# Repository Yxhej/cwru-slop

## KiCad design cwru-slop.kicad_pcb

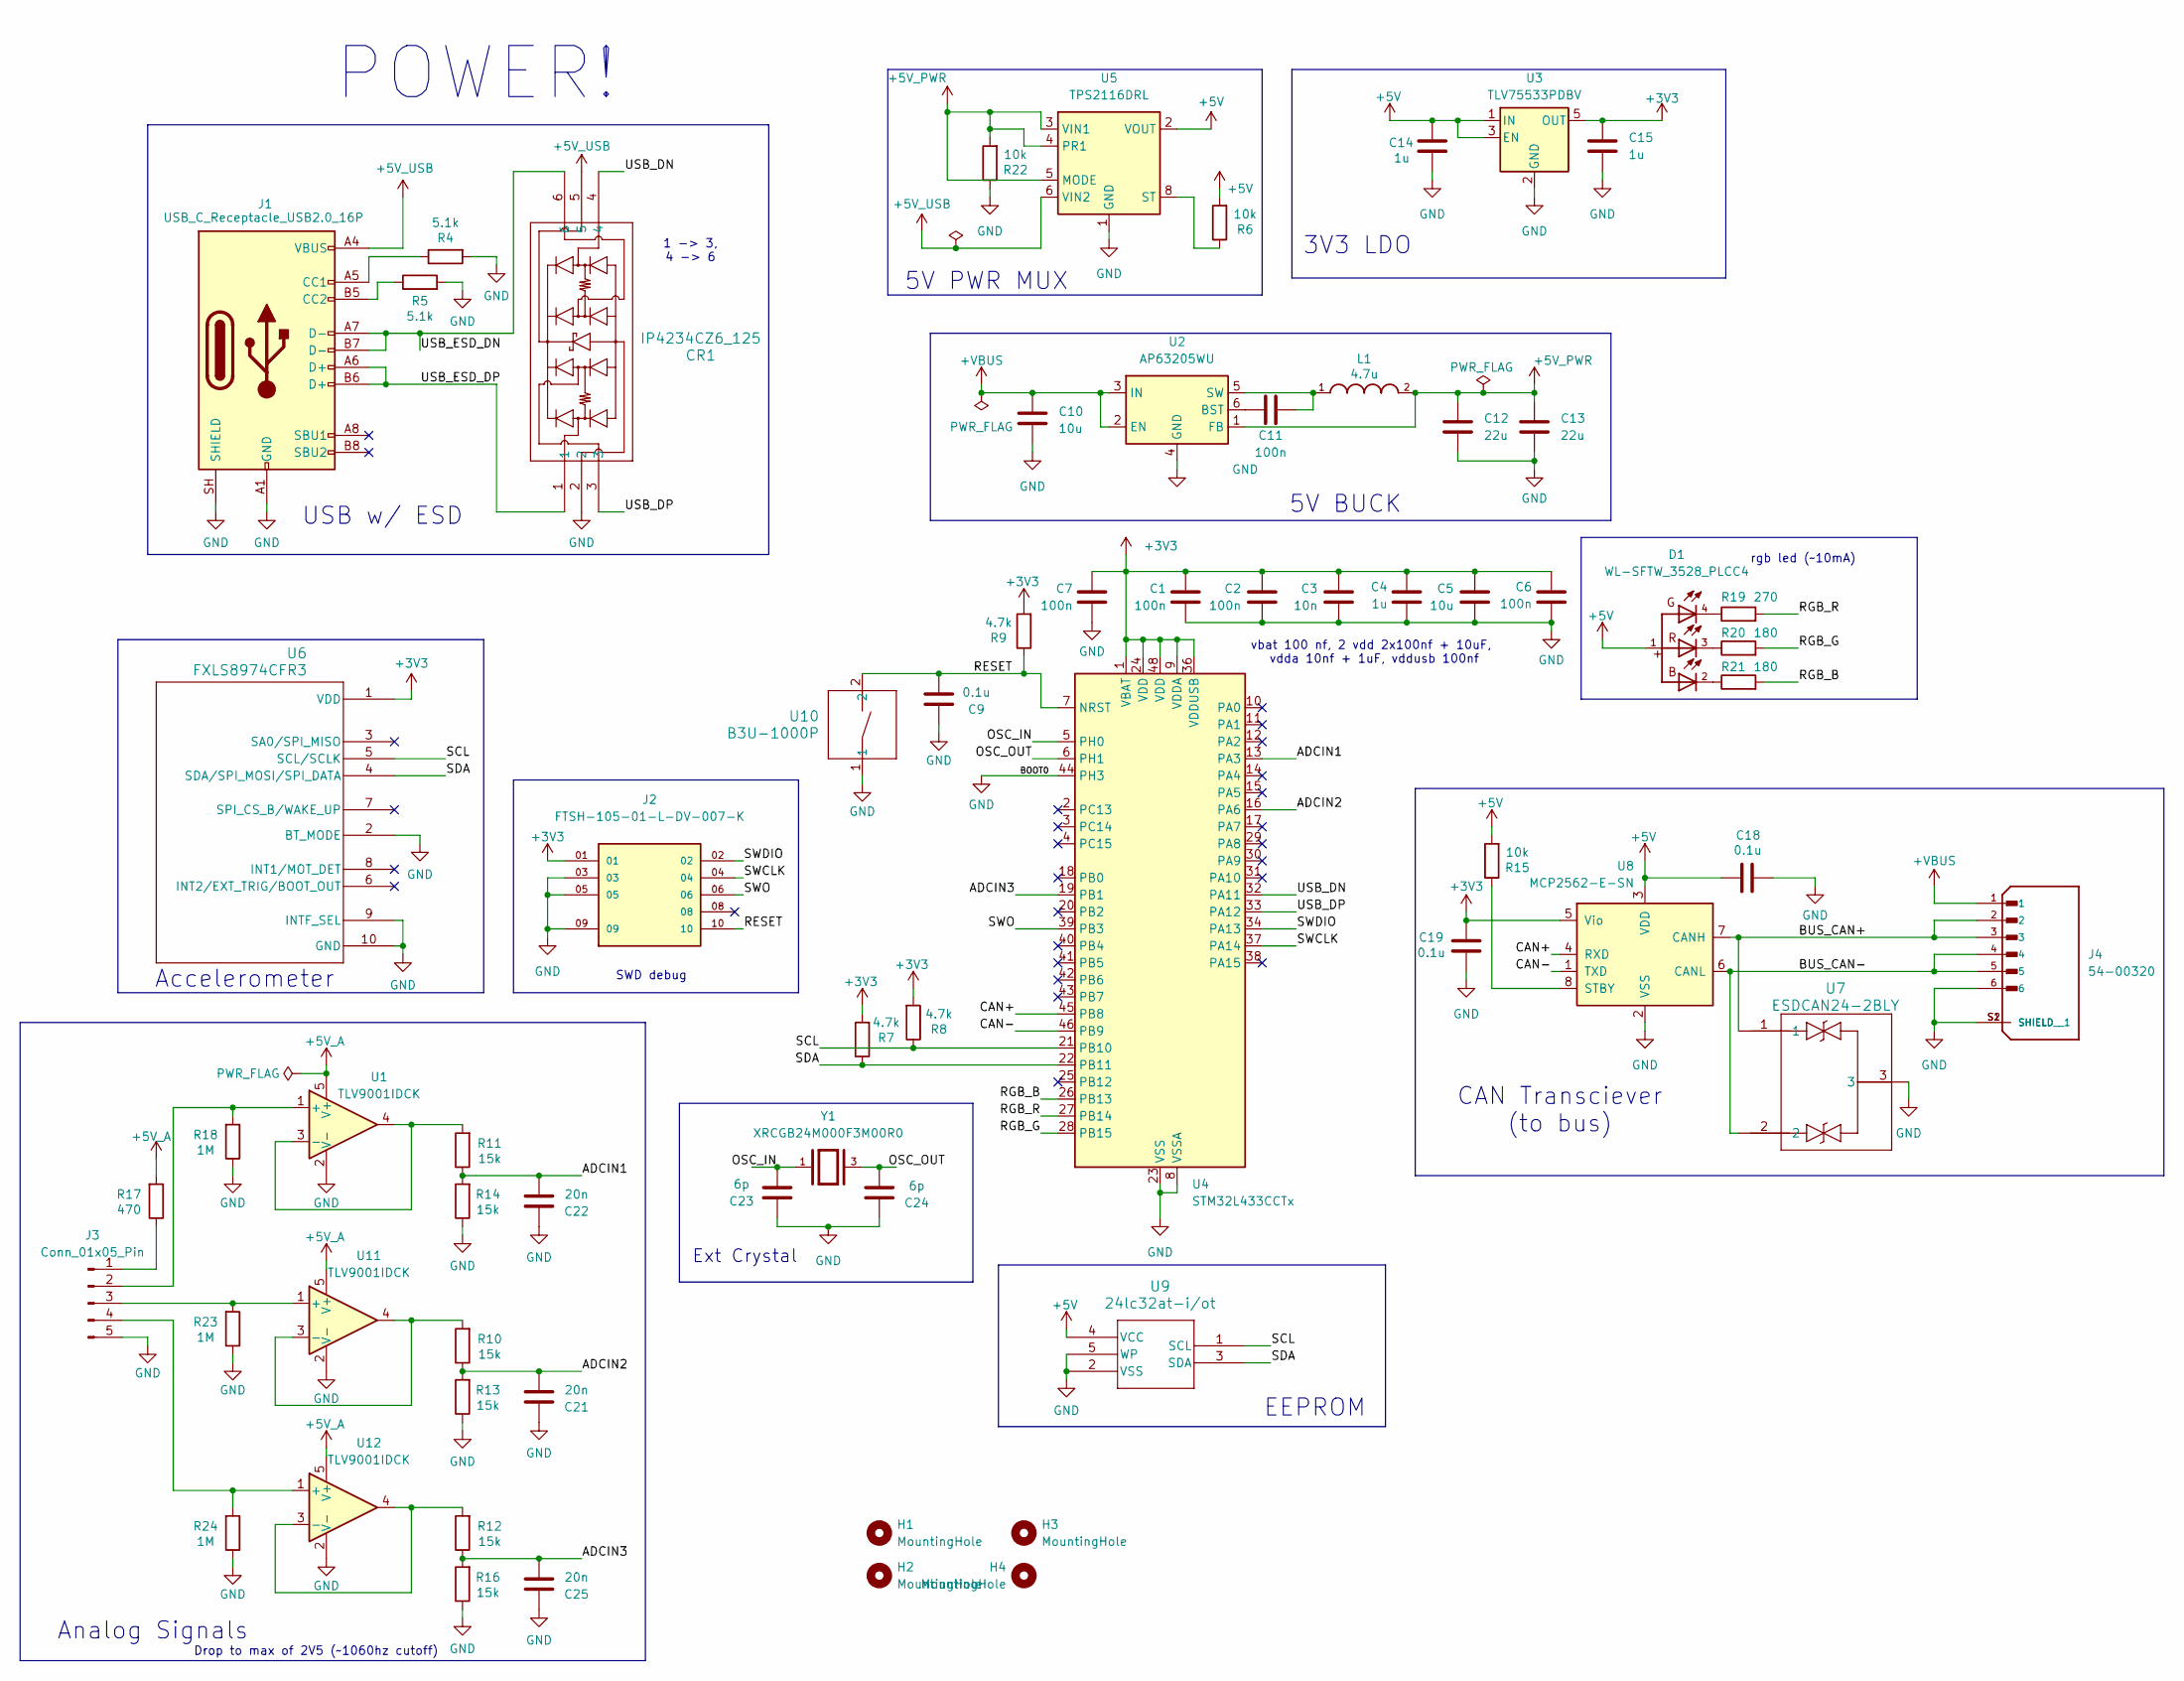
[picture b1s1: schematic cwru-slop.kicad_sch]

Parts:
C1, C2, C6, C7, C11: 100n; C_0603_1608Metric_Pad1.08x0.95mm_HandSolder
C3: 10n; C_0603_1608Metric_Pad1.08x0.95mm_HandSolder
C4, C14, C15: 1u; C_0603_1608Metric_Pad1.08x0.95mm_HandSolder
C5, C10: 10u; C_0603_1608Metric_Pad1.08x0.95mm_HandSolder
C9, C18, C19: 0.1u; C_0603_1608Metric_Pad1.08x0.95mm_HandSolder
C12, C13: 22u; C_0603_1608Metric_Pad1.08x0.95mm_HandSolder
C21, C22, C25: 20n; C_0603_1608Metric_Pad1.08x0.95mm_HandSolder
C23, C24: 6p; C_0603_1608Metric_Pad1.08x0.95mm_HandSolder
CR1: IP4234CZ6_125; TSOP6_SOT457_NEX
D1: WL-SFTW_3528_PLCC4
H1, H2, H3, H4: MountingHole; MountingHole_2.2mm_M2
J1: USB_C_Receptacle_USB2.0_16P; USB_C_Receptacle_GCT_USB4105-xx-A_16P_TopMnt_Horizontal
J2: FTSH-105-01-L-DV-007-K; SAMTEC_FTSH-105-01-L-DV-007-K; PARTREV H
J3: Conn_01x05_Pin; PinHeader_1x05_P2.54mm_Vertical
J4: 54-00320; TENSILITY_54-00320; PARTREV A
L1: 4.7u; INDC2520X120N
R4, R5: 5.1k; R_0603_1608Metric_Pad0.98x0.95mm_HandSolder
R6, R15, R22: 10k; R_0603_1608Metric_Pad0.98x0.95mm_HandSolder
R7, R8, R9: 4.7k; R_0603_1608Metric_Pad0.98x0.95mm_HandSolder
R10, R11, R12, R13, R14, R16: 15k; R_0603_1608Metric_Pad0.98x0.95mm_HandSolder
R17: 470; R_0603_1608Metric_Pad0.98x0.95mm_HandSolder
R18, R23, R24: 1M; R_0603_1608Metric_Pad0.98x0.95mm_HandSolder
R19: 270; R_0603_1608Metric_Pad0.98x0.95mm_HandSolder
R20, R21: 180; R_0603_1608Metric_Pad0.98x0.95mm_HandSolder
U1, U11, U12: TLV9001IDCK; SOT-353_SC-70-5
U2: AP63205WU; TSOT-23-6
U3: TLV75533PDBV; SOT-23-5
U4: STM32L433CCTx; LQFP-48_7x7mm_P0.5mm
U5: TPS2116DRL; SOT-583-8
U6: FXLS8974CFR3; DFN10_2X2_STM
U7: ESDCAN24-2BLY; SOT_24-2BLY_STM
U8: MCP2562-E-SN; SOIC-8_3.9x4.9mm_P1.27mm
U9: 24lc32at-i/ot; SOT-24-5_MC_MCH
U10: B3U-1000P
Y1: XRCGB24M000F3M00R0; OSC_XRCGB24M000F3M00R0; PARTREV N/A

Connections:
+3V3: C1.1, C2.1, C3.1, C4.1, C5.1, C6.1, C7.1, C15.1, C19.2, J2.01, R7.2, R8.2, R9.2, U3.5 (OUT), U4.1 (VBAT), U4.9 (VDDA), U4.24 (VDD), U4.36 (VDDUSB), U4.48 (VDD), U6.1 (VDD), U8.5 (Vio)
+5V: C14.1, C18.1, D1.1, R6.2, R15.2, U3.1 (IN), U3.3 (EN), U5.2 (VOUT), U5.7 (VOUT), U8.3 (VDD), U9.4 (VCC)
+5V_A: R17.2, U1.5 (V+), U11.5 (V+), U12.5 (V+)
+5V_PWR: C12.1, C13.2, L1.2, R22.2, U2.1 (FB), U5.3 (VIN1), U5.4 (PR1), U5.5 (MODE)
+5V_USB: CR1.5, J1.A4 (VBUS), J1.A9 (VBUS), J1.B4 (VBUS), J1.B9 (VBUS), U5.6 (VIN2)
+VBUS: C10.1, J4.1, U2.2 (EN), U2.3 (IN)
/ADCIN1: C22.2, R11.1, R14.2, U4.13 (PA3)
/ADCIN2: C21.2, R10.1, R13.2, U4.16 (PA6)
/ADCIN3: C25.2, R12.1, R16.2, U4.19 (PB1)
/BUS_CAN+: J4.2, J4.3, U7.1, U8.7 (CANH)
/BUS_CAN-: J4.4, J4.5, U7.2, U8.6 (CANL)
/CAN+: U4.45 (PB8), U8.4 (RXD)
/CAN-: U4.46 (PB9), U8.1 (TXD)
/OSC_IN: C23.2, U4.5 (PH0), Y1.1
/OSC_OUT: C24.2, U4.6 (PH1), Y1.3
/RESET: C9.2, J2.10, R9.1, U4.7 (NRST), U10.2
/RGB_B: R21.2, U4.26 (PB13)
/RGB_G: R20.2, U4.28 (PB15)
/RGB_R: R19.2, U4.27 (PB14)
/SCL: R8.1, U4.21 (PB10), U6.5 (SCL/SCLK), U9.1 (SCL)
/SDA: R7.1, U4.22 (PB11), U6.4 (SDA/SPI_MOSI/SPI_DATA), U9.3 (SDA)
/SWCLK: J2.04, U4.37 (PA14)
/SWDIO: J2.02, U4.34 (PA13)
/SWO: J2.06, U4.39 (PB3)
/USB_DN: CR1.4, U4.32 (PA11)
/USB_DP: CR1.3, U4.33 (PA12)
/USB_ESD_DN: CR1.6, J1.A7 (D-), J1.B7 (D-)
/USB_ESD_DP: CR1.1, J1.A6 (D+), J1.B6 (D+)
GND: C1.2, C2.2, C3.2, C4.2, C5.2, C6.2, C7.2, C9.1, C10.2, C12.2, C13.1, C14.2, C15.2, C18.2, C19.1, C21.1, C22.1, C23.1, C24.1, C25.1, CR1.2, J1.A1 (GND), J1.A12 (GND), J1.B1 (GND), J1.B12 (GND), J1.SH (SHIELD), J2.03, J2.05, J2.09, J3.5, J4.6, J4.S1 (SHIELD), J4.S2 (SHIELD__1), R4.2, R5.2, R13.1, R14.1, R16.1, R18.1, R22.1, R23.1, R24.1, U1.2 (V-), U2.4 (GND), U3.2 (GND), U4.8 (VSSA), U4.23 (VSS), U4.35 (VSS), U4.44 (PH3), U4.47 (VSS), U5.1 (GND), U6.2 (BT_MODE), U6.9 (INTF_SEL), U6.10 (GND), U7.3, U8.2 (VSS), U9.2 (VSS), U9.5 (WP), U10.1, U11.2 (V-), U12.2 (V-)
unnamed: D1.2, R21.1
unnamed: D1.3, R20.1
unnamed: D1.4, R19.1
unnamed: J1.A5 (CC1), R4.1
unnamed: J1.B5 (CC2), R5.1
unnamed: J3.1, R17.1
unnamed: J3.2, R18.2, U1.1 (+)
unnamed: J3.3, R23.2, U11.1 (+)
unnamed: J3.4, R24.2, U12.1 (+)
unnamed: R11.2, U1.3 (-), U1.4
unnamed: C11.1, U2.6 (BST)
unnamed: C11.2, L1.1, U2.5 (SW)
unnamed: R6.1, U5.8 (ST)
unnamed: R15.1, U8.8 (STBY)
unnamed: R10.2, U11.3 (-), U11.4
unnamed: R12.2, U12.3 (-), U12.4

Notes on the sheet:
Ext Crystal
3V3 LDO
CAN Transciever (to bus)
5V BUCK
Drop to max of 2V5 (~1060hz cutoff)
Analog Signals
rgb led (~10mA)
5V PWR MUX
POWER!
USB w/ ESD
vbat 100 nf, 2 vdd 2x100nf + 10uF, vdda 10nf + 1uF, vddusb 100nf
SWD debug
1 -> 3, 4 -> 6
EEPROM
Accelerometer

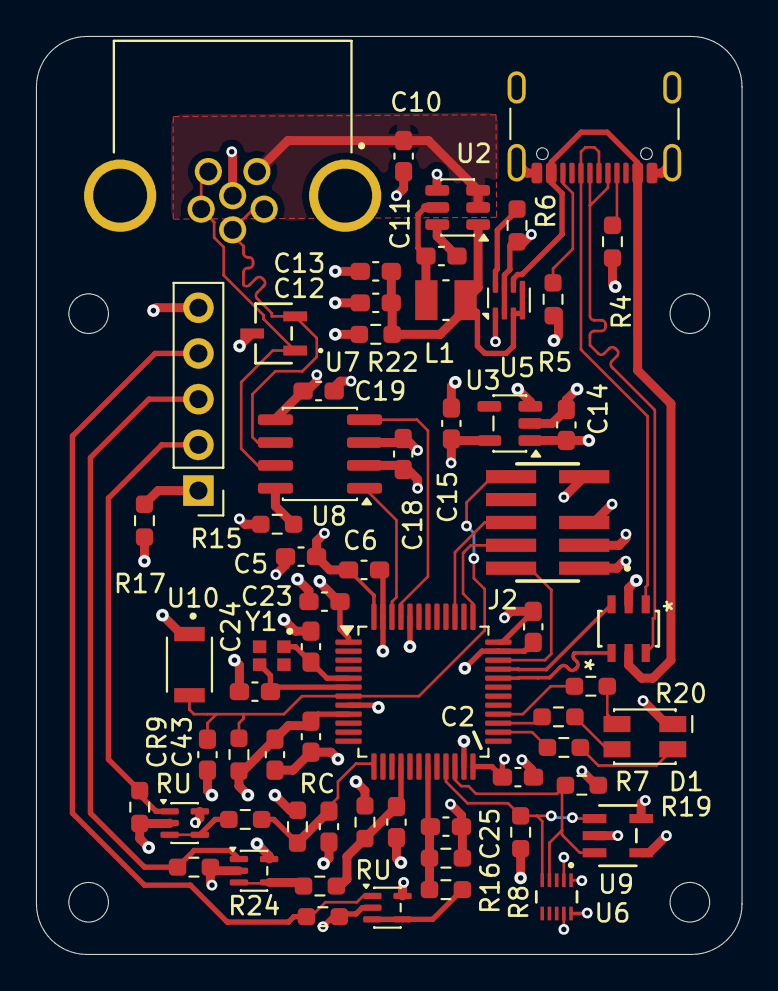
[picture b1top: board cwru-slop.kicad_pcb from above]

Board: 4 copper layers, 39.2 x 51.0 mm, 66 parts (0 on the bottom side), 45 nets.

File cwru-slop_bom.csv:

Designator,Footprint,Quantity,Value,LCSC Part #
"C1, C11, C2, C6, C7",0603,5,100n,
"C10, C5",0603,2,10u,
"C12, C13",0603,2,22u,
"C14, C15, C4",0603,3,1u,
"C18, C19, C9",0603,3,0.1u,
"C21, C22, C25",0603,3,20n,
"C23, C24",0603,2,6p,
C3,0603,1,10n,
CR1,TSOP6_SOT457_NEX,1,IP4234CZ6_125,
D1,WL-SFTW_3528_PLCC4,1,WL-SFTW_3528_PLCC4,
J1,USB_C_Receptacle_GCT_USB4105-xx-A_16P_TopMnt_Horizontal,1,USB_C_Receptacle_USB2.0_16P,
J2,SAMTEC_FTSH-105-01-L-DV-007-K,1,FTSH-105-01-L-DV-007-K,
J3,PinHeader_1x05_P2.54mm_Vertical,1,Conn_01x05_Pin,
J4,TENSILITY_54-00320,1,54-00320,
L1,INDC2520X120N,1,4.7u,
"R10, R11, R12, R13, R14, R16",0603,6,15k,
"R15, R22, R6",0603,3,10k,
R17,0603,1,470,
"R18, R23, R24",0603,3,1M,
R19,0603,1,270,
"R20, R21",0603,2,180,
"R4, R5",0603,2,5.1k,
"R7, R8, R9",0603,3,4.7k,
"U1, U11, U12",SOT-353_SC-70-5,3,TLV9001IDCK,
U10,B3U-1000P,1,B3U-1000P,
U2,TSOT-23-6,1,AP63205WU,
U3,SOT-23-5,1,TLV75533PDBV,
U4,LQFP-48_7x7mm_P0.5mm,1,STM32L433CCTx,
U5,SOT-583-8,1,TPS2116DRL,
U6,DFN10_2X2_STM,1,FXLS8974CFR3,
U7,SOT_24-2BLY_STM,1,ESDCAN24-2BLY,
U8,SOIC-8_3.9x4.9mm_P1.27mm,1,MCP2562-E-SN,
U9,SOT-24-5_MC_MCH,1,24lc32at-i/ot,
Y1,OSC_XRCGB24M000F3M00R0,1,XRCGB24M000F3M00R0,

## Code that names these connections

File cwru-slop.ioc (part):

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Mcu.Name=STM32L433C(B-C)Tx
Mcu.Package=LQFP48
Mcu.UserName=STM32L433CCTx
PA11.Mode=Device
PA11.Signal=USB_DM
PA12.Mode=Device
PA12.Signal=USB_DP
PA13\ (JTMS-SWDIO).Signal=SYS_JTMS-SWDIO
PA14\ (JTCK-SWCLK).Signal=SYS_JTCK-SWCLK
PA3.Signal=ADCx_IN8
PA6.Signal=ADCx_IN11
PB1.Signal=ADCx_IN16
PB10.Mode=I2C
PB10.Signal=I2C2_SCL
PB11.Mode=I2C
PB11.Signal=I2C2_SDA
PB13.Signal=GPIO_Output
PB14.Signal=GPIO_Output
PB15.Signal=GPIO_Output
PB3\ (JTDO-TRACESWO).Signal=SYS_JTDO-SWO
PB8.Mode=CAN_Activate
PB8.Signal=CAN1_RX
PB9.Mode=CAN_Activate
PB9.Signal=CAN1_TX
PH0-OSC_IN\ (PH0).Mode=HSE-External-Oscillator
PH0-OSC_IN\ (PH0).Signal=RCC_OSC_IN
PH1-OSC_OUT\ (PH1).Mode=HSE-External-Oscillator
PH1-OSC_OUT\ (PH1).Signal=RCC_OSC_OUT
RCC.HSE_VALUE=8000000
RCC.SYSCLKFreq_VALUE=80000000
RCC.SYSCLKSource=RCC_SYSCLKSOURCE_PLLCLK
board=custom
